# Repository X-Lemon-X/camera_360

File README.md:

# 360 camera

## PCB  design

# CXmara hanfdling
# list all video devices
```bash
v4l2-ctl --list-devices
```
# list all video formats
```bash
v4l2-ctl --list-formats-ext
```
# list all video controls
```bash
v4l2-ctl -d /dev/video0 --list-ctrls
```

# play video
```bash
ffplay -f v4l2 -input_format mjpeg -framerate 30 -video_size 3840x2160 -fflags nobuffer -vf "vflip" /dev/video0
```

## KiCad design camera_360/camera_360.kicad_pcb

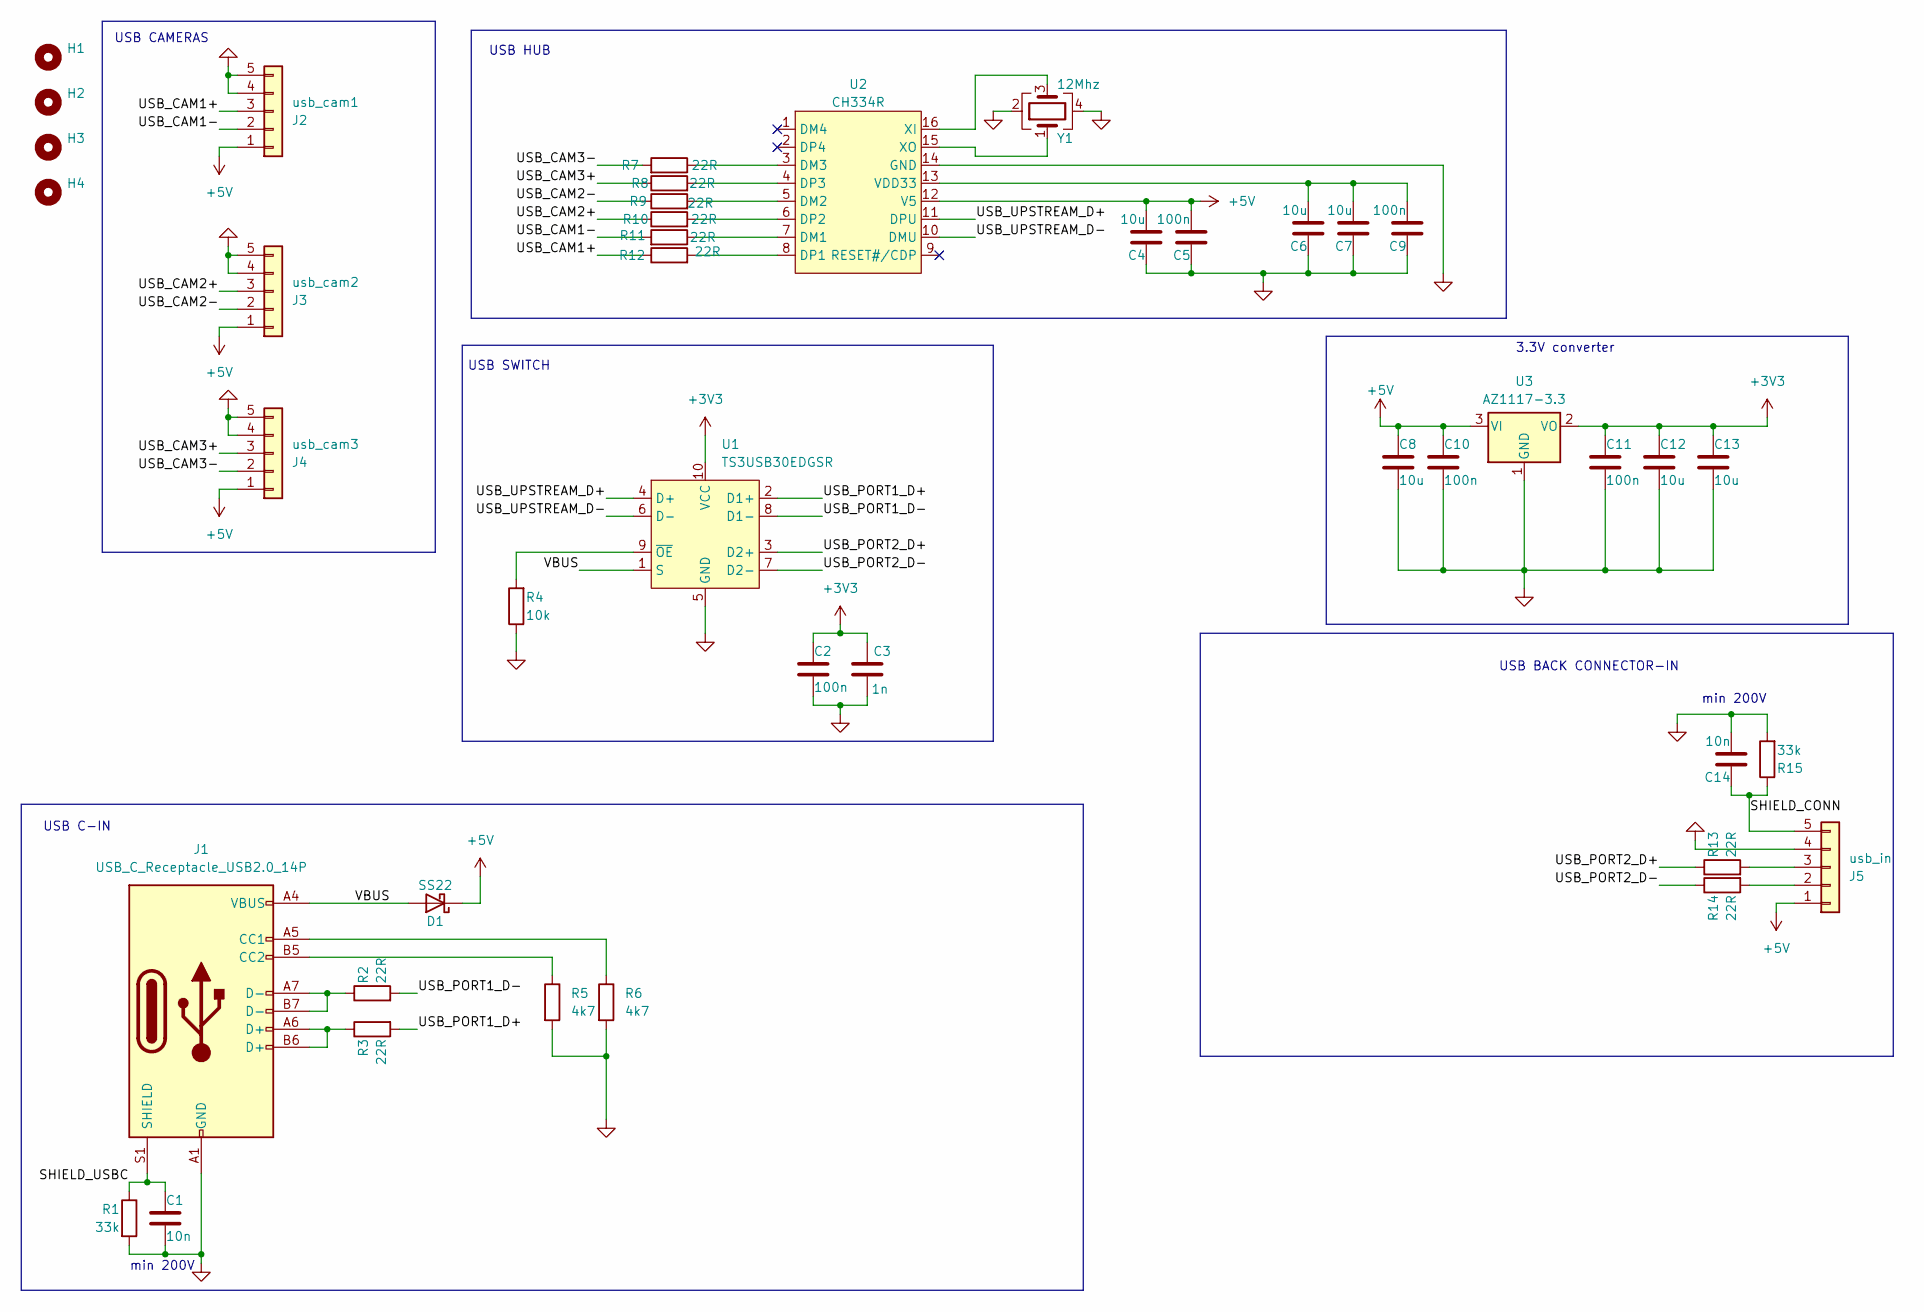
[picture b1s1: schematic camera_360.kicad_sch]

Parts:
C1, C14: 10n; C_0805_2012Metric
C2, C5, C9: 100n; C_0402_1005Metric
C3: 1n; C_0402_1005Metric
C4, C6, C7, C8, C12, C13: 10u; C_0805_2012Metric
C10, C11: 100n; C_0603_1608Metric
D1: SS22; D_SMA
H1, H2, H3, H4: MountingHole; MountingHole_3.2mm_M3_DIN965_Pad
J1: USB_C_Receptacle_USB2.0_14P; USB_C_Receptacle_G-Switch_GT-USB-7010ASV
J2: usb_cam1; JST_GH_BM05B-GHS-TBT_1x05-1MP_P1.25mm_Vertical
J3: usb_cam2; JST_GH_BM05B-GHS-TBT_1x05-1MP_P1.25mm_Vertical
J4: usb_cam3; JST_GH_BM05B-GHS-TBT_1x05-1MP_P1.25mm_Vertical
J5: usb_in; JST_GH_BM05B-GHS-TBT_1x05-1MP_P1.25mm_Vertical
R1, R15: 33k; R_0603_1608Metric
R2, R3, R7, R8, R9, R10, R11, R12, R13, R14: 22R; R_0402_1005Metric
R4: 10k; R_0402_1005Metric
R5, R6: 4k7; R_0402_1005Metric
U1: TS3USB30EDGSR; VSSOP-10_3x3mm_P0.5mm
U2: CH334R; QSOP-16_3.9x4.9mm_P0.635mm
U3: AZ1117-3.3; SOT-223-3_TabPin2
Y1: 12Mhz; Crystal_SMD_3225-4Pin_3.2x2.5mm

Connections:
+3V3: C2.1, C3.1, C11.1, C12.1, C13.1, U1.10 (VCC), U3.2 (VO)
+5V: C4.2, C5.2, C8.1, C10.1, D1.1 (K), J2.1, J3.1, J4.1, J5.1, U2.12 (V5), U3.3 (VI)
/SHIELD_CONN: C14.1, J5.5, R15.1
/SHIELD_USBC: C1.1, J1.S1 (SHIELD), R1.1
/USB_CAM1+: J2.3, R12.1
/USB_CAM1-: J2.2, R11.2
/USB_CAM2+: J3.3, R10.1
/USB_CAM2-: J3.2, R9.1
/USB_CAM3+: J4.3, R8.1
/USB_CAM3-: J4.2, R7.2
/USB_PORT1_D+: R3.2, U1.2 (D1+)
/USB_PORT1_D-: R2.2, U1.8 (D1-)
/USB_PORT2_D+: R13.1, U1.3 (D2+)
/USB_PORT2_D-: R14.1, U1.7 (D2-)
/USB_UPSTREAM_D+: U1.4 (D+), U2.11 (DPU)
/USB_UPSTREAM_D-: U1.6 (D-), U2.10 (DMU)
/VBUS: D1.2 (A), J1.A4 (VBUS), J1.A9 (VBUS), J1.B4 (VBUS), J1.B9 (VBUS), U1.1 (S)
GND: C1.2, C2.2, C3.2, C4.1, C5.1, C6.1, C7.1, C8.2, C9.1, C10.2, C11.2, C12.2, C13.2, C14.2, J1.A1 (GND), J1.A12 (GND), J1.B1 (GND), J1.B12 (GND), J2.4, J2.5, J2.MP, J3.4, J3.5, J3.MP, J4.4, J4.5, J4.MP, J5.4, J5.MP, R1.2, R4.1, R5.2, R6.2, R15.2, U1.5 (GND), U2.14 (GND), U3.1 (GND), Y1.2, Y1.4
unnamed: J1.A5 (CC1), R6.1
unnamed: J1.B5 (CC2), R5.1
unnamed: J1.A6 (D+), J1.B6 (D+), R3.1
unnamed: J1.A7 (D-), J1.B7 (D-), R2.1
unnamed: J5.2, R14.2
unnamed: J5.3, R13.2
unnamed: R4.2, U1.9 (~OE)
unnamed: R11.1, U2.7 (DM1)
unnamed: R9.2, U2.5 (DM2)
unnamed: R7.1, U2.3 (DM3)
unnamed: R12.2, U2.8 (DP1)
unnamed: R10.2, U2.6 (DP2)
unnamed: R8.2, U2.4 (DP3)
unnamed: C6.2, C7.2, C9.2, U2.13 (VDD33)
unnamed: U2.16 (XI), Y1.3
unnamed: U2.15 (XO), Y1.1

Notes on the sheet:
3.3V converter
USB CAMERAS
USB BACK CONNECTOR-IN
min 200V
USB C-IN
USB SWITCH
USB HUB

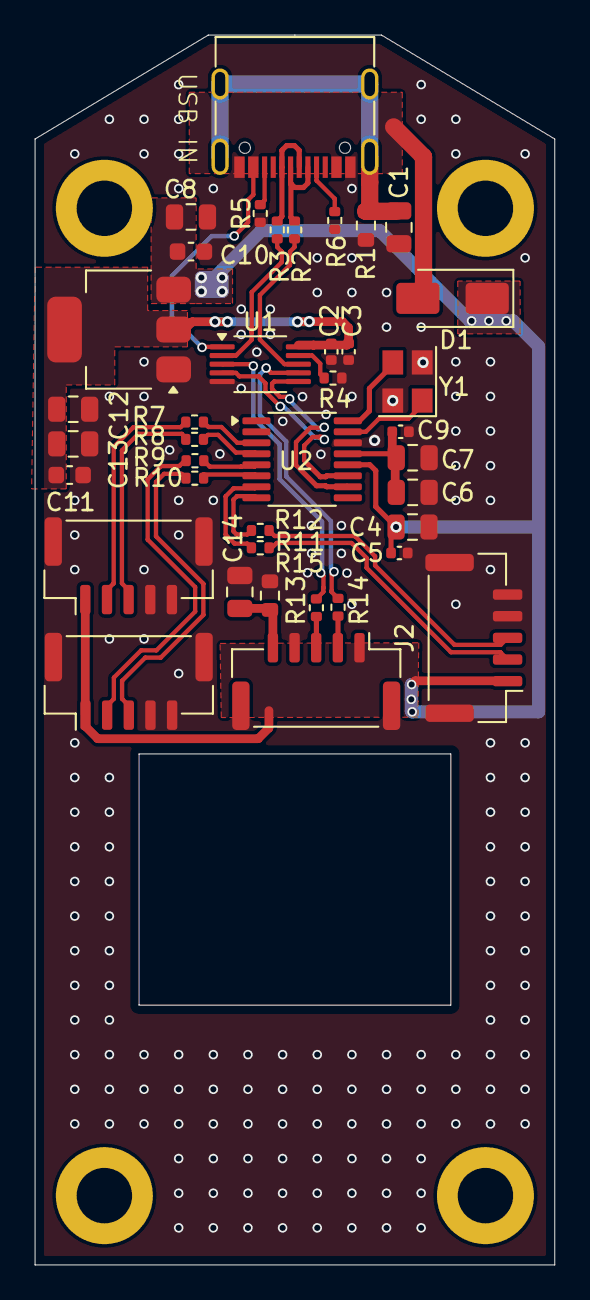
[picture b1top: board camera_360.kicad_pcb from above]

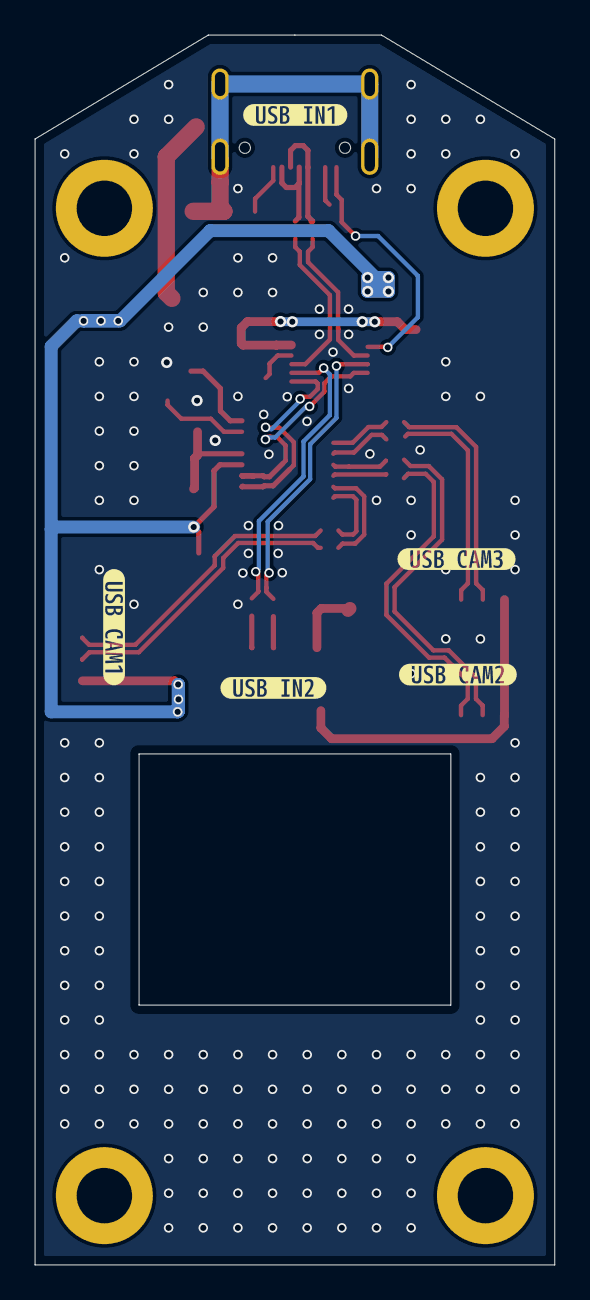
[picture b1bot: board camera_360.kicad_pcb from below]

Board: 2 copper layers, 30.0 x 71.0 mm, 48 parts (5 on the bottom side), 34 nets.

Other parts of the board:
kibuzzard-6782C8D8: G***; kibuzzard-6782C8D8
kibuzzard-6782C8DC: G***; kibuzzard-6782C8DC
kibuzzard-6782C80A: G***; kibuzzard-6782C80A
kibuzzard-6782C81A: G***; kibuzzard-6782C81A
kibuzzard-6782C82D: G***; kibuzzard-6782C82D

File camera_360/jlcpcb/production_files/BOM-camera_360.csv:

Comment,Designator,Footprint,LCSC,Quantity
22R,R2,R_0402_1005Metric,,1
22R,R3,R_0402_1005Metric,,1
22R,R14,R_0402_1005Metric,,1
22R,R13,R_0402_1005Metric,,1
AZ1117-3.3,U3,SOT-223-3_TabPin2,,1
10u,C13,C_0805_2012Metric,,1
10u,C12,C_0805_2012Metric,,1
100n,C11,C_0603_1608Metric,,1
100n,C10,C_0603_1608Metric,,1
10u,C8,C_0805_2012Metric,,1
TS3USB30EDGSR,U1,VSSOP-10_3x3mm_P0.5mm,,1
10k,R4,R_0402_1005Metric,,1
SS22,D1,D_SMA,,1
1n,C3,C_0402_1005Metric,,1
100n,C2,C_0402_1005Metric,,1
10n,C14,C_0805_2012Metric,,1
33k,R15,R_0603_1608Metric,,1
usb_in,J5,JST_GH_BM05B-GHS-TBT_1x05-1MP_P1.25mm_Vertical,,1
usb_cam2,J3,JST_GH_BM05B-GHS-TBT_1x05-1MP_P1.25mm_Vertical,,1
22R,R8,R_0402_1005Metric,,1
33k,R1,R_0603_1608Metric,,1
22R,R12,R_0402_1005Metric,,1
USB_C_Receptacle_USB2.0_14P,J1,USB_C_Receptacle_G-Switch_GT-USB-7010ASV,,1
100n,C9,C_0402_1005Metric,,1
22R,R10,R_0402_1005Metric,,1
100n,C5,C_0402_1005Metric,,1
usb_cam3,J4,JST_GH_BM05B-GHS-TBT_1x05-1MP_P1.25mm_Vertical,,1
22R,R7,R_0402_1005Metric,,1
10u,C6,C_0805_2012Metric,,1
22R,R11,R_0402_1005Metric,,1
22R,R9,R_0402_1005Metric,,1
10n,C1,C_0805_2012Metric,,1
CH334R,U2,QSOP-16_3.9x4.9mm_P0.635mm,,1
10u,C7,C_0805_2012Metric,,1
10u,C4,C_0805_2012Metric,,1
4k7,R5,R_0402_1005Metric,,1
12Mhz,Y1,Crystal_SMD_3225-4Pin_3.2x2.5mm,,1
usb_cam1,J2,JST_GH_BM05B-GHS-TBT_1x05-1MP_P1.25mm_Vertical,,1
4k7,R6,R_0402_1005Metric,,1

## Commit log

2024-11-22 init
2024-11-22 REV 2. added usb c abd essd protection
2024-12-08 final revA
2024-12-14 update usb difff apirs and added vias
2024-12-16 Final rev
2025-01-11 chaged uusb connectro to jst mx1.25
